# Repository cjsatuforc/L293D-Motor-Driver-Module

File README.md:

# L293D-Motor-Driver-Module
A dual motor driver module compatible with Arduino, Raspberry Pi, ESP family, etc

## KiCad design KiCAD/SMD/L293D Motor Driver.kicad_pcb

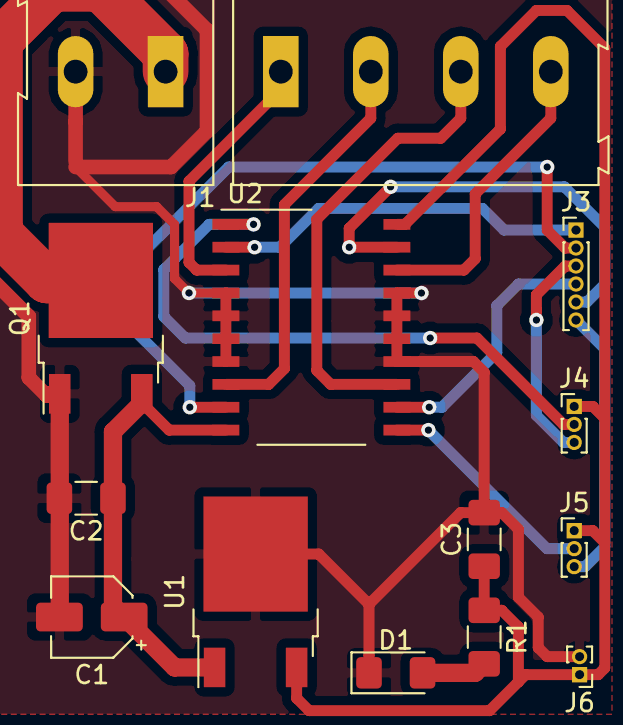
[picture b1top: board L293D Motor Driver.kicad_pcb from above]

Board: 2 copper layers, 14 parts (0 on the bottom side), 17 nets.

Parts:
C1: 47uF 16V; CP_Elec_4x5.8
C2: 0.33uF; C_1206_3216Metric_Pad1.42x1.75mm_HandSolder
C3: 0.1uF'; C_1206_3216Metric_Pad1.42x1.75mm_HandSolder
D1: LED; LED_1206_3216Metric_Pad1.42x1.75mm_HandSolder
J1: Supply; TerminalBlock_Altech_AK300-2_P5.00mm
J2: Motors; TerminalBlock_Altech_AK300-4_P5.00mm
J3: Logic; PinHeader_1x06_P1.00mm_Vertical
J4: EN1,2; PinHeader_1x03_P1.00mm_Vertical
J5: EN3,4; PinHeader_1x03_P1.00mm_Vertical
J6: 5V O/P; PinHeader_1x02_P1.00mm_Vertical
Q1: NVD5117PL; TO-252-2
R1: 220; R_1206_3216Metric_Pad1.42x1.75mm_HandSolder
U1: LM7805_DPAK; TO-252-2
U2: L293DD; SO-20_12.8x7.5mm_P1.27mm

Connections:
5V: C3.1, J4.1, J5.1, J6.1, R1.1, U1.3, U2.20
12V: C1.1, C2.1, Q1.3, U1.1, U2.10
GND: C1.2, C2.2, C3.2, D1.1, J1.2, J6.2, Q1.1, U1.2, U2.4, U2.5, U2.6, U2.7, U2.14, U2.15, U2.16, U2.17
unnamed: D1.2, R1.2
unnamed: J1.1, Q1.2
unnamed: J2.1, U2.3
unnamed: J2.2, U2.8
unnamed: J2.3, U2.13
unnamed: J2.4, U2.18
unnamed: J3.1, U2.2
unnamed: J3.2, U2.9
unnamed: J3.3, J4.3
unnamed: J3.4, U2.12
unnamed: J3.5, U2.19
unnamed: J3.6, J5.3
unnamed: J4.2, U2.1
unnamed: J5.2, U2.11

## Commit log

2019-02-18 KiCAD files
    Board + Schematic
    Img
2019-03-06 Eagle
2019-03-06 Eagle Bottom Only
    For Homemade PCB on single side PCB.
2019-03-06 Update issue templates
    Bug report
2019-03-06 Update issue templates
2019-03-06 Eagle: Printable
2019-03-06 Language
